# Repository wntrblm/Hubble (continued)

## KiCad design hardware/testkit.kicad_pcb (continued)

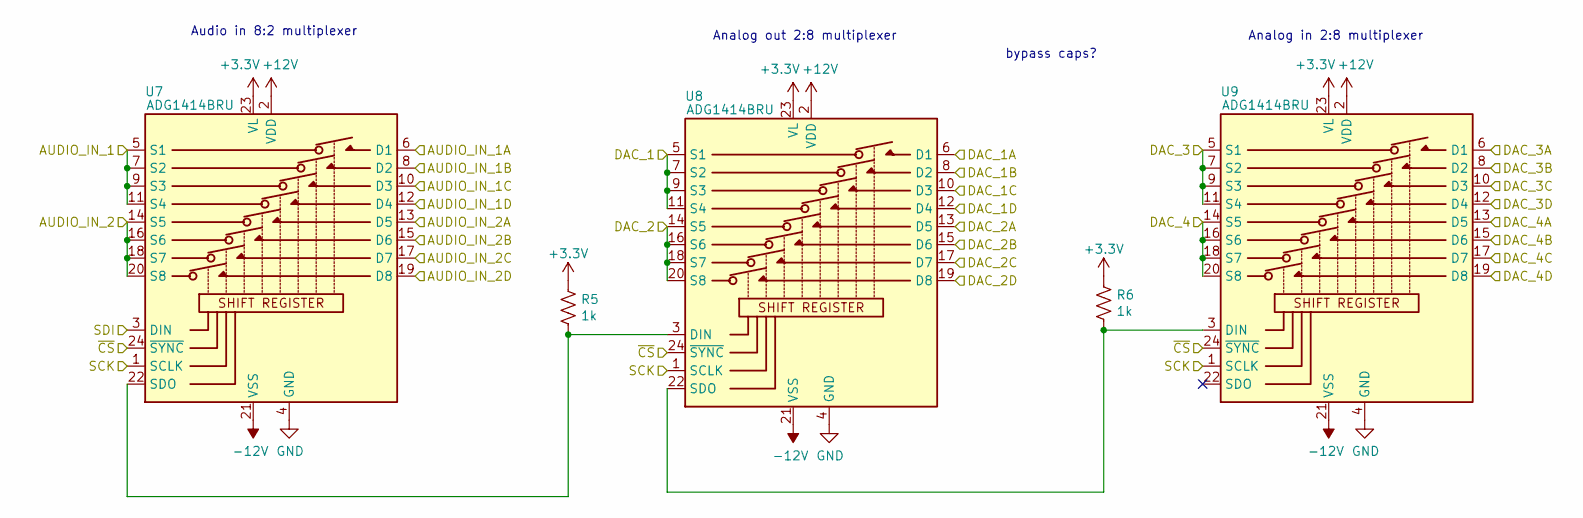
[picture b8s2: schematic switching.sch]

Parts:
R5, R6: 1k; R_0603_1608Metric_Pad0.98x0.95mm_HandSolder
U7, U8, U9: ADG1414BRU; TSSOP-24_4.4x7.8mm_P0.65mm

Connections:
+12V: U7.2 (VDD), U8.2 (VDD), U9.2 (VDD); also elsewhere on the board
-12V: U7.21 (VSS), U8.21 (VSS), U9.21 (VSS); also elsewhere on the board
/AUDIO_IN_1A: U7.6 (D1); also elsewhere on the board
/AUDIO_IN_1B: U7.8 (D2); also elsewhere on the board
/AUDIO_IN_1C: U7.10 (D3); also elsewhere on the board
/AUDIO_IN_1D: U7.12 (D4); also elsewhere on the board
/AUDIO_IN_2A: U7.13 (D5); also elsewhere on the board
/AUDIO_IN_2B: U7.15 (D6); also elsewhere on the board
/AUDIO_IN_2C: U7.17 (D7); also elsewhere on the board
/AUDIO_IN_2D: U7.19 (D8); also elsewhere on the board
/AUDIO_IN_L: U7.5 (S1), U7.7 (S2), U7.9 (S3), U7.11 (S4); also elsewhere on the board
/AUDIO_IN_R: U7.14 (S5), U7.16 (S6), U7.18 (S7), U7.20 (S8); also elsewhere on the board
/DAC_1A: U8.6 (D1); also elsewhere on the board
/DAC_1B: U8.8 (D2); also elsewhere on the board
/DAC_1C: U8.10 (D3); also elsewhere on the board
/DAC_1D: U8.12 (D4); also elsewhere on the board
/DAC_2A: U8.13 (D5); also elsewhere on the board
/DAC_2B: U8.15 (D6); also elsewhere on the board
/DAC_2C: U8.17 (D7); also elsewhere on the board
/DAC_2D: U8.19 (D8); also elsewhere on the board
/DAC_3A: U9.6 (D1); also elsewhere on the board
/DAC_3B: U9.8 (D2); also elsewhere on the board
/DAC_3C: U9.10 (D3); also elsewhere on the board
/DAC_3D: U9.12 (D4); also elsewhere on the board
/DAC_4A: U9.13 (D5); also elsewhere on the board
/DAC_4B: U9.15 (D6); also elsewhere on the board
/DAC_4C: U9.17 (D7); also elsewhere on the board
/DAC_4D: U9.19 (D8); also elsewhere on the board
/Switching/DAC_1: U8.5 (S1), U8.7 (S2), U8.9 (S3), U8.11 (S4); also elsewhere on the board
/Switching/DAC_2: U8.14 (S5), U8.16 (S6), U8.18 (S7), U8.20 (S8); also elsewhere on the board
/Switching/DAC_3: U9.5 (S1), U9.7 (S2), U9.9 (S3), U9.11 (S4); also elsewhere on the board
/Switching/DAC_4: U9.14 (S5), U9.16 (S6), U9.18 (S7), U9.20 (S8); also elsewhere on the board
/Switching/~CS: U7.24 (~SYNC), U8.24 (~SYNC), U9.24 (~SYNC)
GND: U7.4 (GND), U8.4 (GND), U9.4 (GND); also elsewhere on the board
unnamed: R5.2, U7.22 (SDO), U8.3 (DIN)
unnamed: R6.2, U8.22 (SDO), U9.3 (DIN)
SPI_COPI: U7.3 (DIN); also elsewhere on the board
SPI_SCLK: U7.1 (SCLK), U8.1 (SCLK), U9.1 (SCLK); also elsewhere on the board

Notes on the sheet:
Analog in 2:8 multiplexer
Audio in 8:2 multiplexer
Analog out 2:8 multiplexer
bypass caps?

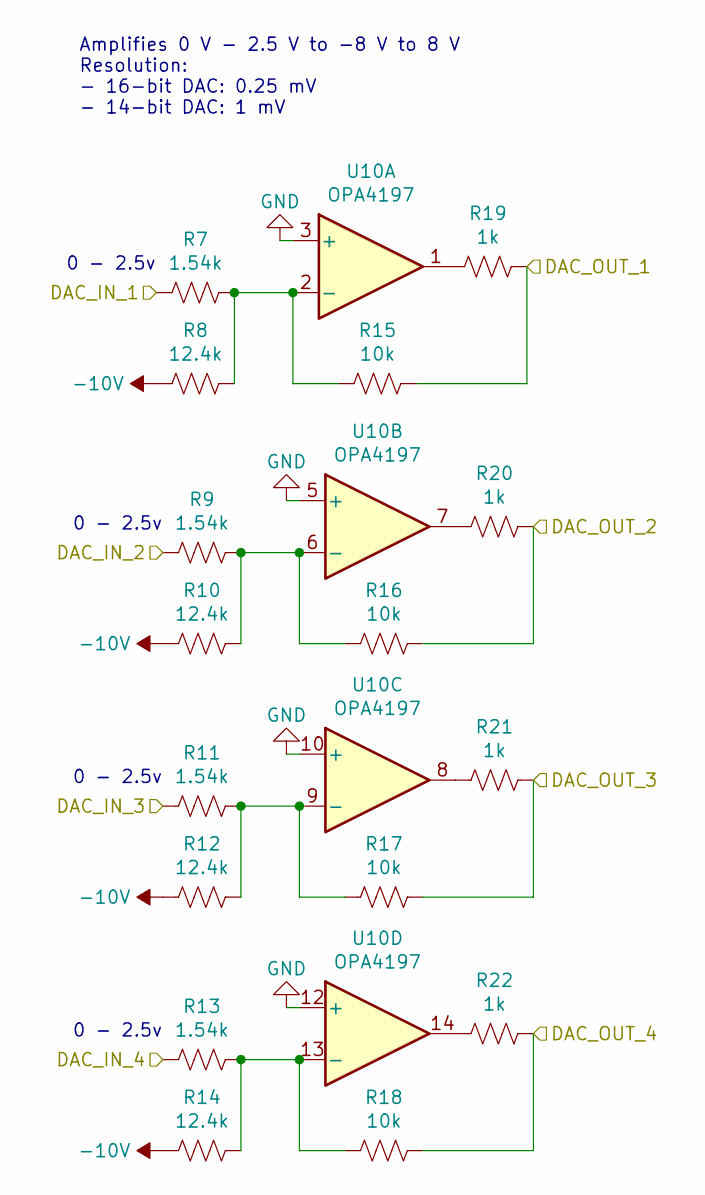
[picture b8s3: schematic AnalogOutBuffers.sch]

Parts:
R7, R9, R11, R13: 1.54k; R_0603_1608Metric_Pad1.05x0.95mm_HandSolder
R8, R10, R12, R14: 12.4k; R_0603_1608Metric_Pad1.05x0.95mm_HandSolder
R15, R16, R17, R18: 10k; R_0603_1608Metric_Pad1.05x0.95mm_HandSolder
R19, R20, R21, R22: 1k; R_0603_1608Metric_Pad1.05x0.95mm_HandSolder
U10: OPA4197; TSSOP-14_4.4x5mm_P0.65mm; mpn OPA4197IPW

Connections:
+12V: U10.4 (V+); also elsewhere on the board
-10V: R8.2, R10.2, R12.2, R14.2; also elsewhere on the board
-12V: U10.11 (V-); also elsewhere on the board
/Switching/DAC_1: R17.1, R21.1; also elsewhere on the board
/Switching/DAC_2: R18.1, R22.1; also elsewhere on the board
/Switching/DAC_3: R15.1, R19.1; also elsewhere on the board
/Switching/DAC_4: R16.1, R20.1; also elsewhere on the board
DAC_1: R7.2; also elsewhere on the board
DAC_2: R9.2; also elsewhere on the board
DAC_3: R11.2; also elsewhere on the board
DAC_4: R13.2; also elsewhere on the board
GND: U10.3 (+), U10.5 (+), U10.10 (+), U10.12 (+); also elsewhere on the board
unnamed: R9.1, R10.1, R16.2, U10.6 (-)
unnamed: R11.1, R12.1, R17.2, U10.9 (-)
unnamed: R13.1, R14.1, R18.2, U10.13 (-)
unnamed: R7.1, R8.1, R15.2, U10.2 (-)
unnamed: R19.2, U10.1
unnamed: R20.2, U10.7
unnamed: R21.2, U10.8
unnamed: R22.2, U10.14

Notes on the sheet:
0 - 2.5v
Amplifies 0 V - 2.5 V to -8 V to 8 V Resolution: - 16-bit DAC: 0.25 mV - 14-bit DAC: 1 mV

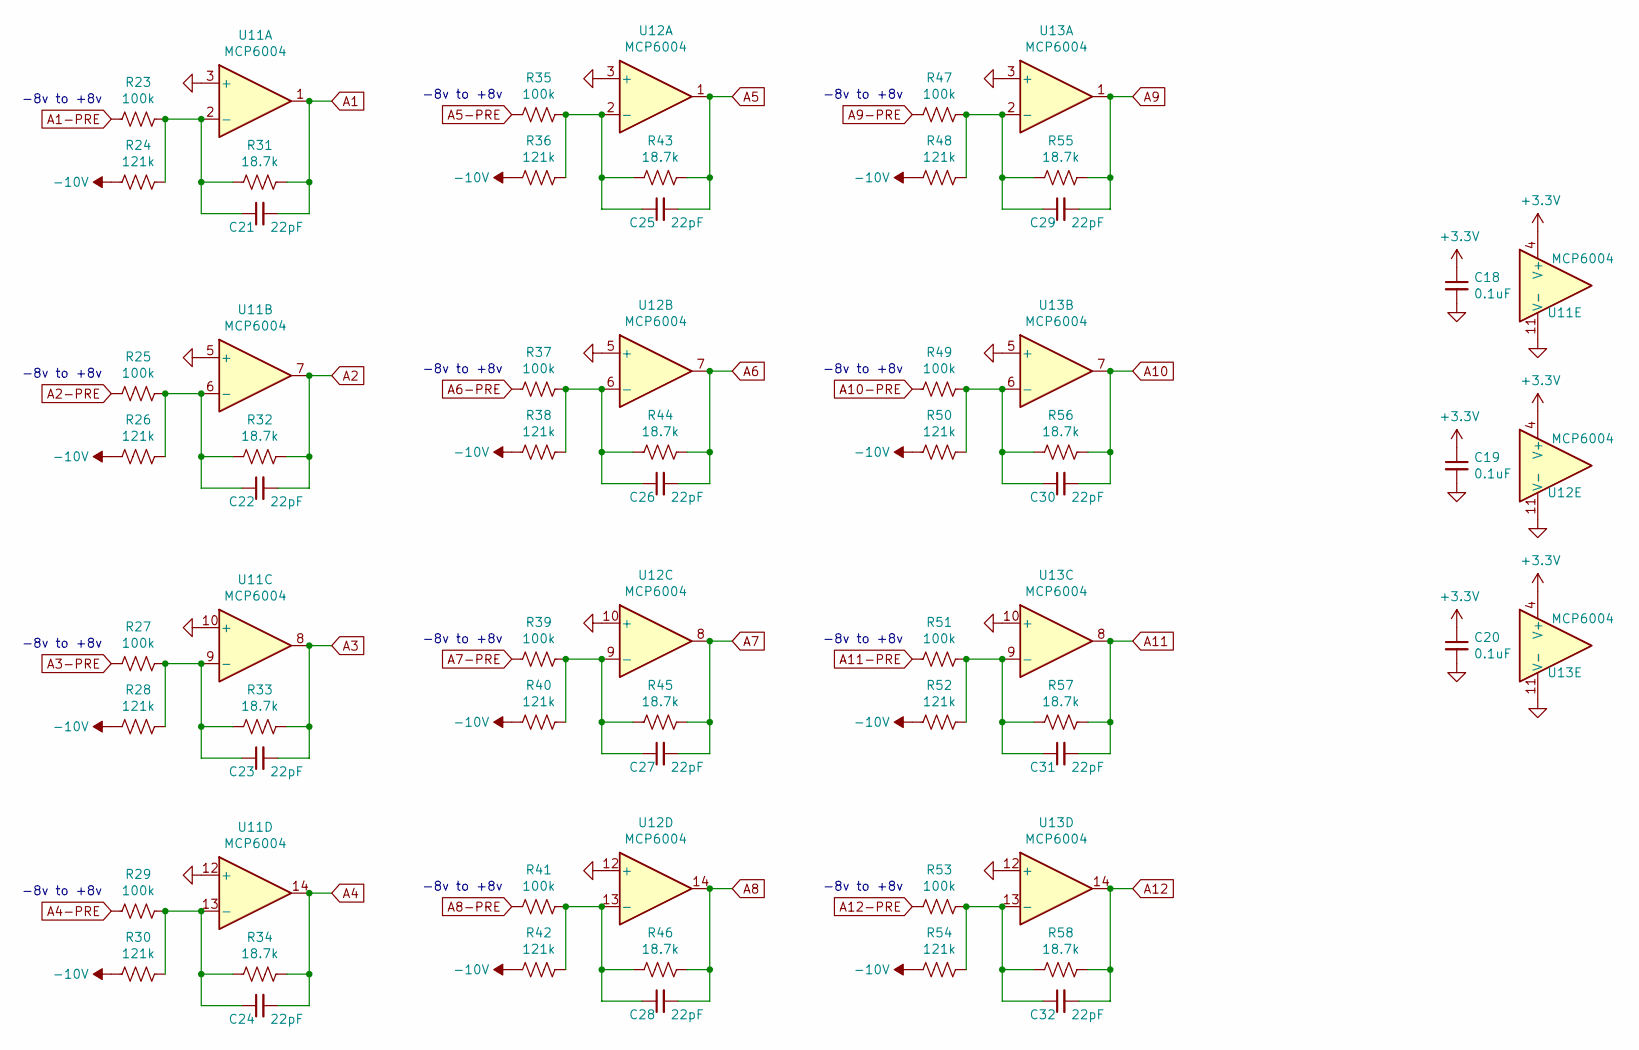
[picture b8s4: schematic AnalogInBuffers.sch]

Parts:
C18, C19, C20: 0.1uF; C_0603_1608Metric_Pad1.08x0.95mm_HandSolder
C21, C22, C23, C24, C25, C26, C27, C28, C29, C30, C31, C32: 22pF; C_0603_1608Metric_Pad1.08x0.95mm_HandSolder
R23, R25, R27, R29, R35, R37, R39, R41, R47, R49, R51, R53: 100k; R_0603_1608Metric_Pad0.98x0.95mm_HandSolder
R24, R26, R28, R30, R36, R38, R40, R42, R48, R50, R52, R54: 121k; R_0603_1608Metric_Pad0.98x0.95mm_HandSolder
R31, R32, R33, R34, R43, R44, R45, R46, R55, R56, R57, R58: 18.7k; R_0603_1608Metric_Pad0.98x0.95mm_HandSolder
U11, U12, U13: MCP6004; TSSOP-14_4.4x5mm_P0.65mm; mpn MCP6004T-I/ST, MCP6004T-E/ST

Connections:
-10V: R24.2, R26.2, R28.2, R30.2, R36.2, R38.2, R40.2, R42.2, R48.2, R50.2, R52.2, R54.2; also elsewhere on the board
A1: C21.2, R31.1, U11.1; also elsewhere on the board
A1-PRE: R23.2; also elsewhere on the board
A2: C22.2, R32.1, U11.7; also elsewhere on the board
A2-PRE: R25.2; also elsewhere on the board
A3: C23.2, R33.1, U11.8; also elsewhere on the board
A3-PRE: R27.2; also elsewhere on the board
A4: C24.2, R34.1, U11.14; also elsewhere on the board
A4-PRE: R29.2; also elsewhere on the board
A5: C25.2, R43.1, U12.1; also elsewhere on the board
A5-PRE: R35.2; also elsewhere on the board
A6: C26.2, R44.1, U12.7; also elsewhere on the board
A6-PRE: R37.2; also elsewhere on the board
A7: C27.2, R45.1, U12.8; also elsewhere on the board
A7-PRE: R39.2; also elsewhere on the board
A8: C28.2, R46.1, U12.14; also elsewhere on the board
A8-PRE: R41.2; also elsewhere on the board
A9: C29.2, R55.1, U13.1; also elsewhere on the board
A9-PRE: R47.2; also elsewhere on the board
A10: C30.2, R56.1, U13.7; also elsewhere on the board
A10-PRE: R49.2; also elsewhere on the board
A11: C31.2, R57.1, U13.8; also elsewhere on the board
A11-PRE: R51.2; also elsewhere on the board
A12: C32.2, R58.1, U13.14; also elsewhere on the board
A12-PRE: R53.2; also elsewhere on the board
GND: C18.2, C19.2, C20.2, U11.3 (+), U11.5 (+), U11.10 (+), U11.11 (V-), U11.12 (+), U12.3 (+), U12.5 (+), U12.10 (+), U12.11 (V-), U12.12 (+), U13.3 (+), U13.5 (+), U13.10 (+), U13.11 (V-), U13.12 (+); also elsewhere on the board
unnamed: C21.1, R23.1, R24.1, R31.2, U11.2 (-)
unnamed: C22.1, R25.1, R26.1, R32.2, U11.6 (-)
unnamed: C23.1, R27.1, R28.1, R33.2, U11.9 (-)
unnamed: C24.1, R29.1, R30.1, R34.2, U11.13 (-)
unnamed: C25.1, R35.1, R36.1, R43.2, U12.2 (-)
unnamed: C26.1, R37.1, R38.1, R44.2, U12.6 (-)
unnamed: C27.1, R39.1, R40.1, R45.2, U12.9 (-)
unnamed: C28.1, R41.1, R42.1, R46.2, U12.13 (-)
unnamed: C29.1, R47.1, R48.1, R55.2, U13.2 (-)
unnamed: C30.1, R49.1, R50.1, R56.2, U13.6 (-)
unnamed: C31.1, R51.1, R52.1, R57.2, U13.9 (-)
unnamed: C32.1, R53.1, R54.1, R58.2, U13.13 (-)

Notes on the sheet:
-8v to +8v

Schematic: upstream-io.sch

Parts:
J8: AUDIO IN; Jack_3.5mm_CUI_SJ1-3533NG_Horizontal
J9: AUDIO OUT; Jack_3.5mm_CUI_SJ1-3533NG_Horizontal
J12: OSC A; Jack_3.5mm_CUI_SJ1-3533NG_Horizontal
J13: OSC B; Jack_3.5mm_CUI_SJ1-3533NG_Horizontal
J14: OSC C; Jack_3.5mm_CUI_SJ1-3533NG_Horizontal
J15: OSC D; Jack_3.5mm_CUI_SJ1-3533NG_Horizontal

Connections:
/AUDIO_IN_L: J8.T; also elsewhere on the board
/AUDIO_IN_R: J8.R; also elsewhere on the board
/AUDIO_OUT_L: J9.T; also elsewhere on the board
/AUDIO_OUT_R: J9.R; also elsewhere on the board
/OSC_A: J12.T; also elsewhere on the board
/OSC_B: J13.T; also elsewhere on the board
/OSC_C: J14.T; also elsewhere on the board
/OSC_D: J15.T; also elsewhere on the board
GND: J8.S, J9.S, J12.R, J12.S, J13.R, J13.S, J14.R, J14.S, J15.R, J15.S; also elsewhere on the board

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
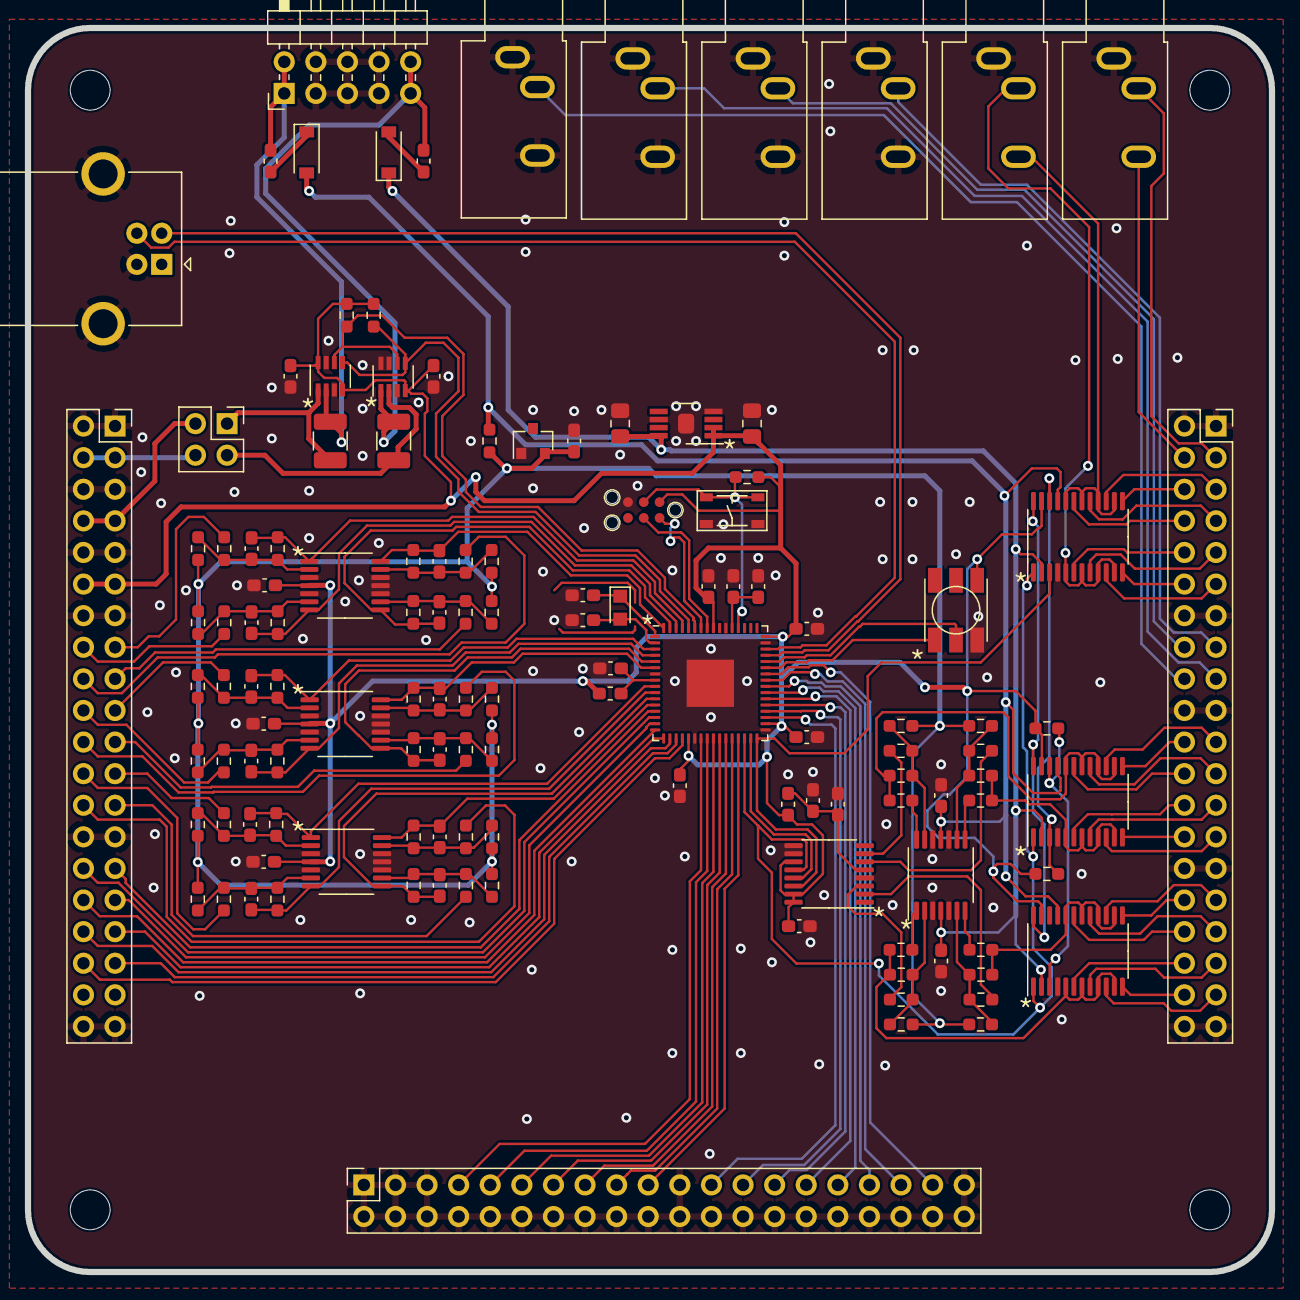
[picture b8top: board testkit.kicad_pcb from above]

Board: 2 copper layers, 100.0 x 100.0 mm, 129 parts (0 on the bottom side), 140 nets.

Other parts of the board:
C33, C34: 0.1uF; C_0603_1608Metric_Pad1.08x0.95mm_HandSolder

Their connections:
+12V: C34.1; also elsewhere on the board
-12V: C33.2; also elsewhere on the board
GND: C33.1, C34.2; also elsewhere on the board

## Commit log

2021-09-10 Initial commit; unfinished, just saving some stuff before making some big design changes
2021-09-21 Add .gitignore
2021-09-21 Finish up first plausible version
2021-09-28 Copy binary star's firmware as a starting point
2021-09-28 Remove sim, build, experimental
2021-09-28 Stripped-down program
2021-09-28 Fix launch stuff and dotstar pin assignments
2021-09-28 Add ADC to stel_config.h
2021-09-28 Basic ADC functionality
2021-09-28 Basic DAC functionality
2021-10-03 Fixup clock initialization
2021-10-03 Remove QSPI region from linker script
2021-10-03 Update dac driver with notes about hardware issues
2021-10-03 Update config with proper ADC inputs and SPI configuration
2021-10-03 Sercom SPI now takes a const struct pointer
2021-10-03 Make AD5685 driver use passed-in SPI instance
2021-10-03 Add driver for adg1414
2021-10-03 Make note that I forgot to wire up CS for the switches
2021-10-05 Screaming into the void
2021-10-08 Add a bunch of breakout boards
2021-10-20 Fix labels on analog in buffers
2021-10-26 Add note about range resistors
2021-10-26 Add pull-ups
2021-10-26 Re-do the motherboard
2021-11-12 Fix issues found in hardware v1
2021-11-12 Add BOD33
2021-11-12 Remove ADG1414 drivers
2021-11-12 Switch 120MHz clock to reference the 1MHz clock instead of the 32kHz clock
2021-11-12 Add BOD33 & clock initialization to SystemInit()
2021-11-12 Update DAC driver to use external analog reference
2021-11-12 Set CS pin to output in AD5685 driver
2021-11-12 Update main/config with stuff for new revision
2021-11-12 Update build
2021-11-12 Ignore vscode state file
2021-11-12 Ignore vscode file
2021-11-13 Update libwinter
2021-11-13 Update tinyusb
2021-11-14 s/Stellar/Hubble
2021-11-14 Add SysEx commands
2021-11-14 Actually add MIDI sysex dispatching
2021-11-14 Add debug print for sysex 0x07
2021-11-15 Add license, readme, etc.
2021-11-15 Move breakouts into their own folder
2021-11-15 Rename Testkit board to Hubble
2021-11-16 Add -Wno-format-nonliteral
2021-11-16 Mark device as self-powered
2021-11-16 Fix GCLK1 SRC parameter
2021-11-16 Copy entire build info array
2021-11-17 Add pack/unpack for float
2021-11-17 Add pragma once
2021-11-17 Add basic DAC calibration
2021-11-18 Fixup some stuff on the motherboard
2021-11-18 Add wntr_debug.h with wntr_debug_print_mem() helper
2021-11-18 Add hubble_nvm for writing to SAMD51 flash
2021-11-18 Reserve more RAM for RTT
2021-11-18 Format
2021-11-18 Basic NVM test
2021-11-18 Reserve space for NVM
2021-11-18 Add basic load/save calibration table
2021-11-18 Add missing print to save_calibration_table
2021-11-19 Up the number of available sysex commands
2021-11-19 Finish up VoltageCalibrationTable loading & saving
2021-11-20 More updates to the board design
    - Added polyfuses for downstream power
    - Added breakout header for external, panel-mounted USB port
    - Added I/O breakout for the switches and buttons on the front control panel
    - Made the MCU footprint a hybrid QFP/QFN footprint
    - Add a nice illustration to the board backside
2021-11-20 Ignore ./logs
2021-11-20 wntr_debug: Use decimal for the size of the memory being printed
2021-11-20 Use decimal when printing the length of a calibration table
2021-11-20 Fix bug where the size of the nvm_buf_ was incorrect
2021-11-20 - Swap channel and mux argument order for sysex commands - Add command for enabling/disabling calibration tables - Extend the length of the DAC calibration table to 16 entries
2021-11-20 Refilled zones
2021-11-22 Fixup some 3dmodel stuff
2021-11-22 Add IO lens
2021-11-22 Add WNTR_ARRAY_LEN macro
2021-11-27 Sync up with upstream libwinter
2021-11-27 Move sysex utils to libwinter
2021-11-28 Move data converter helpers to libwinter
2021-11-28 Move stuff in hw into libwinter/samd51
2021-11-29 Add include directory to c_cpp_properties.json
2021-11-29 Add calibration tables for all four DACs
2021-12-08 Add mechanical designs
2021-12-08 Add ADC calibration tables
2021-12-08 Add basic scripts for calibrating the ADC & DAC
2021-12-08 Add Hubble Python library
2021-12-12 Move python to python_library and add front-panel interface
2021-12-12 Add circuitpython code for the front panel
2021-12-18 firmware: Make sure DACs are set to near-zero at startup
2021-12-18 python library: add formatting and linting
2021-12-18 Add __main__ that drops into IPython shell
2021-12-18 Add ohno
2022-01-01 Update front and back laser cutter templates
2022-01-01 Update design files to KiCAD 6
2022-01-03 Change MIDI name for front panel
2022-01-03 Move motherboard firmware src into its own directory
2022-01-03 Update mechanical design files
2023-06-29 fixup DigitalIO.device, change MIDI_PORT_NAME for Pico
2023-11-08 Fix some minor issues with the Python library
2023-12-30 Initial stab at hardware revision
2024-01-11 plot
2024-02-02 Update libwinter, get things building again
2024-02-02 Change pin assignments
2024-02-02 Change MCU
2024-02-02 Update dostars to use SERCOM SPI
2024-02-02 Get SERCOM6 working
2024-02-02 Cleanup ADC pin defs
2024-02-02 Factor out calibration tables
2024-02-02 Update resistor values in Vout DAC buffers
2024-02-02 Get GPIO working
2024-02-02 Get ADC working
